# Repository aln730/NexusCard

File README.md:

# RP2350 Smart Business Card

A custom PCB business card featuring:

- USB HID functionality  
- Micro-OLED display  
- NFC tag with static UID switching  
- IR transmitter  
- Rechargeable via USB-C  

---

## To-Do

### Hardware

- [x] Select microcontroller (RP2350)
- [x] Choose OLED display (I2C)
- [ ] Add NFC tag with static UID toggle
- [ ] Add IR transmitter (38kHz)
- [x] Include USB-C port with CC resistors
- [ ] Add TP4056 for battery charging
- [x] Design schematic in KiCad
- [ ] Route PCB to standard card size (85mm x 54mm)
- [ ] Order and assemble test PCBs

### Firmware

- [ ] Set up base project with Pico SDK
- [ ] Implement USB HID (keyboard)
- [ ] Drive OLED with simple menu/UI
- [ ] Handle NFC UID switching via GPIO
- [ ] IR transmission with known codes
- [ ] Optional: battery monitoring

### Documentation

- [ ] KiCad schematic and layout
- [ ] Bill of Materials (BOM)
- [ ] Assembly instructions
- [ ] Flashing/programming guide
- [ ] Demo and usage examples

---

## Goals

- Compact, hackable, sci-fi-themed business card
- Show off skills as a computer engineer
- Functional gadget, not just a card

---

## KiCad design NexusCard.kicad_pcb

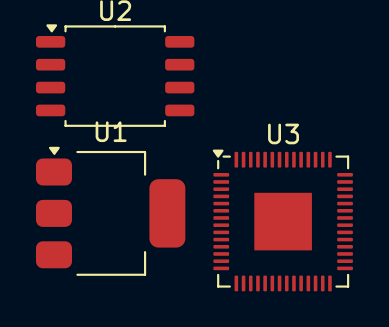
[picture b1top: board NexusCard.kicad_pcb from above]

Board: 2 copper layers, 3 parts (0 on the bottom side), 3 nets, no tracks yet.

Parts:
U1: NCP1117-1.5_SOT223; SOT-223-3_TabPin2
U2: W25Q128JVS; SOIC-8_5.3x5.3mm_P1.27mm
U3: RP2040; QFN-56-1EP_7x7mm_P0.4mm_EP3.2x3.2mm

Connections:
+1V1: U3.23 (DVDD), U3.45 (VREG_VOUT), U3.50 (DVDD)
+3.3V: U1.2 (VO), U2.8 (VCC), U3.1 (IOVDD), U3.10 (IOVDD), U3.22 (IOVDD), U3.33 (IOVDD), U3.42 (IOVDD), U3.43 (ADC_AVDD), U3.44 (VREG_IN), U3.48 (USB_VDD), U3.49 (IOVDD)
GND: U1.1 (GND), U2.4 (GND)

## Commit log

2025-06-02 it aint much but honest work
